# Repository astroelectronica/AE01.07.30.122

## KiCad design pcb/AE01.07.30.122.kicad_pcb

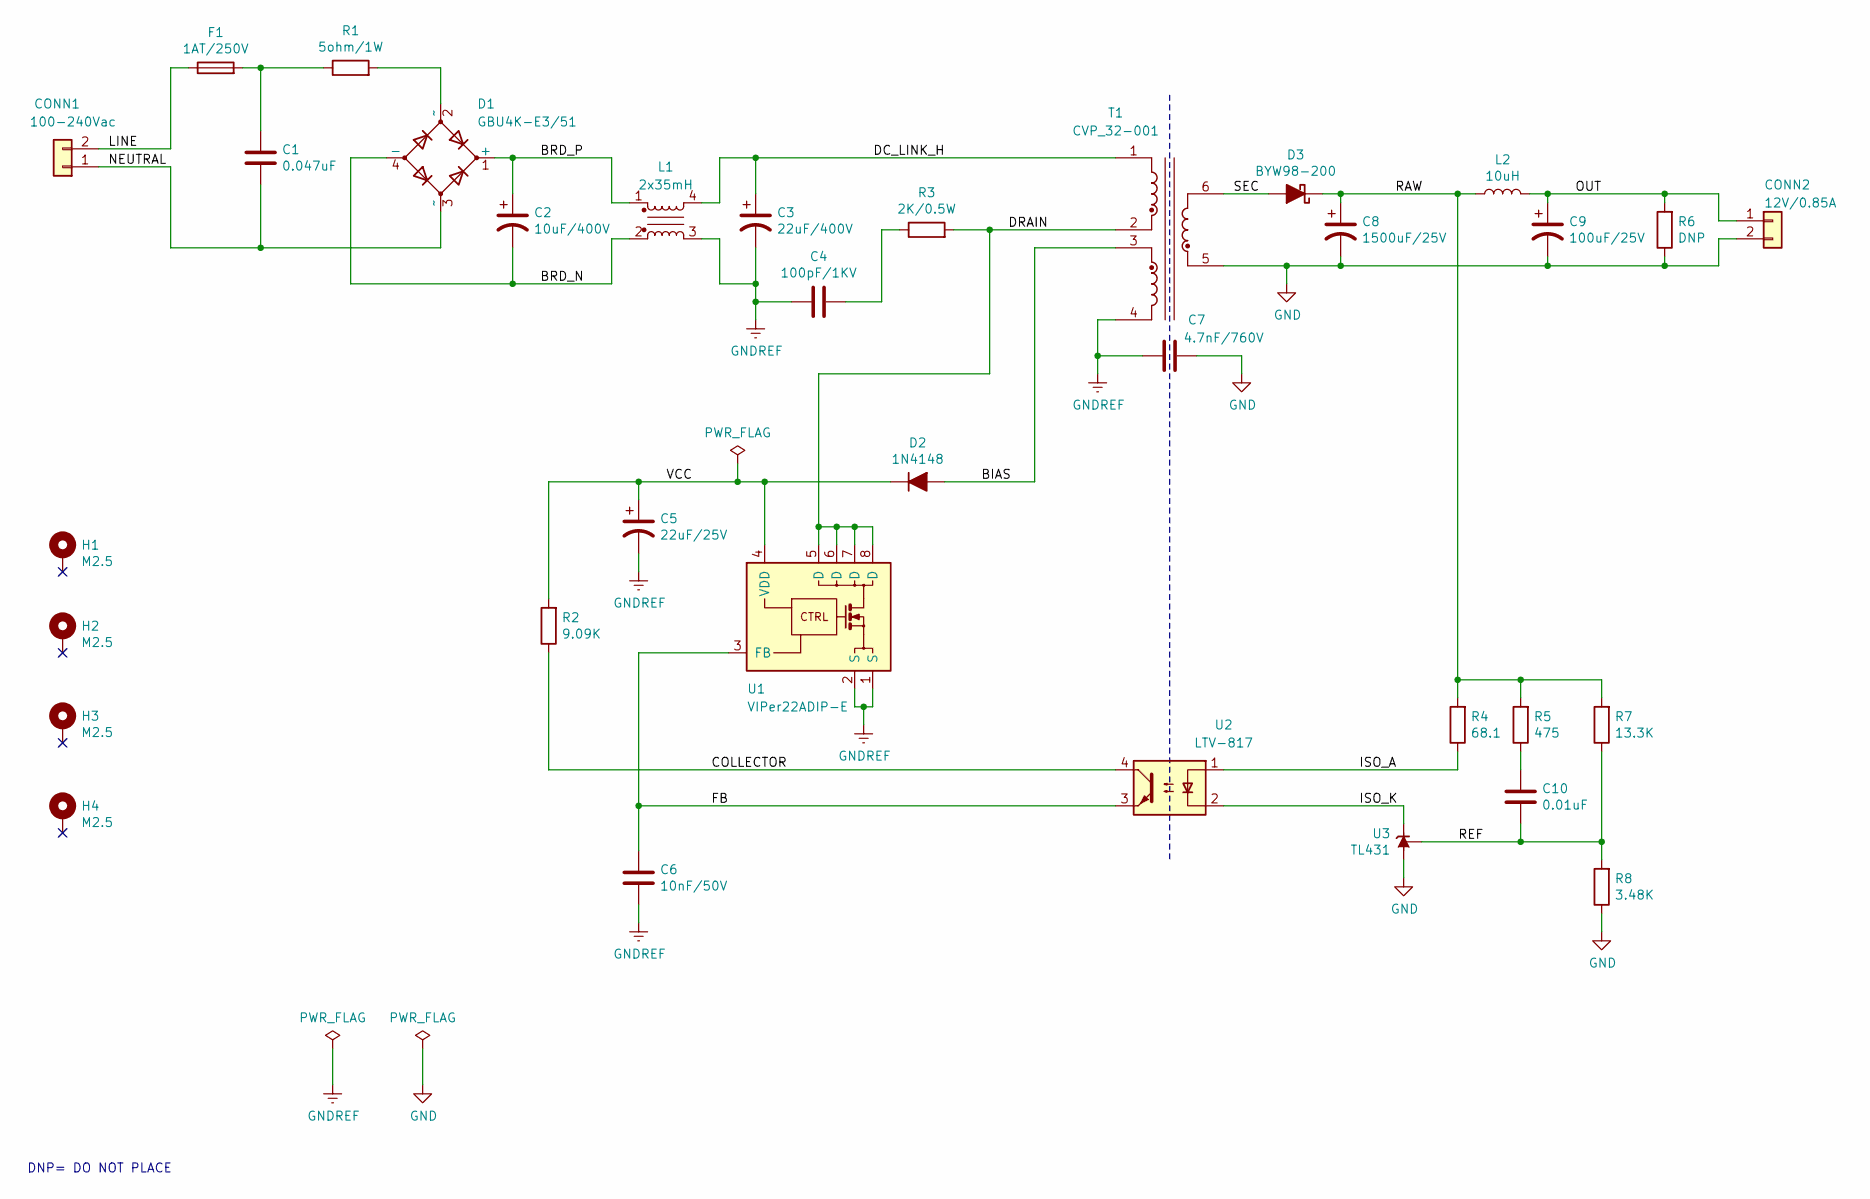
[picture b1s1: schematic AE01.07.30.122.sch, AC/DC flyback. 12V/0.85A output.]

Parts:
C1: 0.047uF; C_Rect_L18.0mm_W5.0mm_P15.00mm_FKS3_FKP3; MPN R46KI24700001K
C2: 10uF/400V; CP_Radial_D10.0mm_P5.00mm_P7.50mm; MPN UCY2G100MPD
C3: 22uF/400V; CP_Radial_D12.5mm_P5.00mm; MPN UCS2G220MHD
C4: 100pF/1KV; C_Disc_D7.5mm_W5.0mm_P5.00mm; MPN F101K25Y5RN63K5R
C5: 22uF/25V; CP_Radial_D6.3mm_P2.50mm; MPN EEA-GA1E220H
C6: 10nF/50V; C_Rect_L7.2mm_W2.5mm_P5.00mm_FKS2_FKP2_MKS2_MKP2; MPN SMR5103J50J01L16.5CBULK
C7: 4.7nF/760V; C_Disc_D16.0mm_W5.0mm_P10.00mm; MPN VY1472M63Y5UQ63V0
C8: 1500uF/25V; CP_Radial_D12.5mm_P5.00mm; MPN EEU-FM1E152
C9: 100uF/25V; CP_Radial_D10.0mm_P2.50mm_P5.00mm; MPN EKRG250ETD101MJ09S
C10: 0.01uF; C_Disc_D5.0mm_W2.5mm_P2.50mm; MPN K103K15X7RF5TL2
CONN1: 100-240Vac; PhoenixContact_GMSTBA_2,5_2-G-7,62_1x02_P7.62mm_Horizontal; MPN 1728853
CONN2: 12V/0.85A; PhoenixContact_GMSTBA_2,5_2-G-7,62_1x02_P7.62mm_Horizontal; MPN 1728853
D1: GBU4K-E3/51; Diode_Bridge_Vishay_GBU; MPN GBU4K-E3/51
D2: 1N4148; D_DO-35_SOD27_P10.16mm_Horizontal; MPN 1N4148TR
D3: BYW98-200; D_DO-201AD_P15.24mm_Horizontal; MPN SB3200TA
F1: 1AT/250V; Fuseholder_Cylinder-5x20mm_Schurter_0031_8201_Horizontal_Op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; MPN 31.8201
H1, H2, H3, H4: M2.5; MountingHole_2.7mm_M2.5_Pad_Via
L1: 2x35mH; L_CommonMode_Wuerth_WE-CMB-NC; MPN 7448040435
L2: 10uH; L_Radial_D8.7mm_P5.00mm_Fastron_07HCP; MPN RLB0914-100KL
R1: 5ohm/1W; R_Axial_DIN0414_L11.9mm_D4.5mm_P20.32mm_Horizontal; MPN ALSR015R000JE12
R2: 9.09K; R_Axial_DIN0207_L6.3mm_D2.5mm_P10.16mm_Horizontal; MPN RNF14FTD9K09
R3: 2K/0.5W; R_Axial_DIN0309_L9.0mm_D3.2mm_P15.24mm_Horizontal; MPN CF12JT2K00
R4: 68.1; R_Axial_DIN0207_L6.3mm_D2.5mm_P10.16mm_Horizontal; MPN RNF14FTD68R1
R5: 475; R_Axial_DIN0207_L6.3mm_D2.5mm_P10.16mm_Horizontal; MPN RNF14FTD475R
R6: DNP; R_Axial_DIN0207_L6.3mm_D2.5mm_P10.16mm_Horizontal
R7: 13.3K; R_Axial_DIN0207_L6.3mm_D2.5mm_P10.16mm_Horizontal; MPN MFR-25FBF52-13K3
R8: 3.48K; R_Axial_DIN0207_L6.3mm_D2.5mm_P10.16mm_Horizontal; MPN MFR-25FBF52-3K48
T1: CVP_32-001; MPN CVP 32-001
U1: VIPer22ADIP-E; DIP-8_W7.62mm; MPN VIPER22ADIP-E
U2: LTV-817; DIP-4_W7.62mm; MPN LTV-817
U3: TL431; TO-92_Inline_Wide; MPN TL431CLPRE3

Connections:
/BIAS: D2.2 (A), T1.3
/BRD_N: C2.2, D1.4 (-), L1.2
/BRD_P: C2.1, D1.1 (+), L1.1
/COLLECTOR: R2.1, U2.4
/DC_LINK_H: C3.1, L1.4, T1.1
/DRAIN: R3.2, T1.2, U1.5 (D), U1.6 (D), U1.7 (D), U1.8 (D)
/FB: C6.1, U1.3 (FB), U2.3
/ISO_A: R4.1, U2.1
/ISO_K: U2.2, U3.3 (K)
/LINE: CONN1.2, F1.1
/NEUTRAL: C1.2, CONN1.1, D1.3 (~~)
/OUT: C9.1, CONN2.1, L2.2, R6.2
/RAW: C8.1, D3.1 (K), L2.1, R4.2, R5.2, R7.2
/REF: C10.2, R7.1, R8.2, U3.1 (REF)
/SEC: D3.2 (A), T1.6
/VCC: C5.1, D2.1 (K), R2.2, U1.4 (VDD)
GND: C7.1, C8.2, C9.2, CONN2.2, R6.1, R8.1, T1.5, U3.2 (A)
GNDREF: C3.2, C4.1, C5.2, C6.2, C7.2, L1.3, T1.4, U1.1 (S), U1.2 (S)
unnamed: C1.1, F1.2, R1.1
unnamed: C4.2, R3.1
unnamed: C10.1, R5.1
unnamed: D1.2 (~~), R1.2

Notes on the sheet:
DNP= DO NOT PLACE

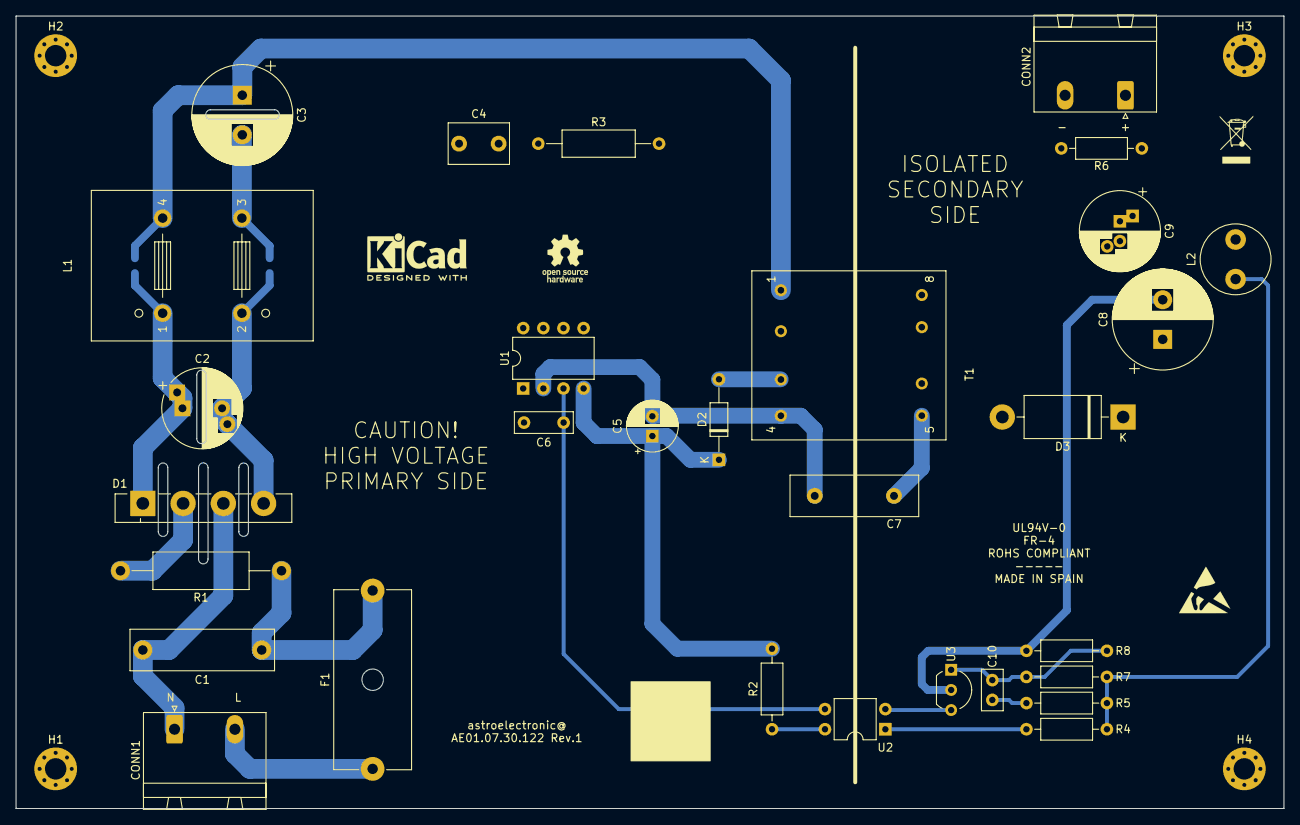
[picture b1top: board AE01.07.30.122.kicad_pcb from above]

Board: 2 copper layers, 160.0 x 100.0 mm, 34 parts (0 on the bottom side), 22 nets.
